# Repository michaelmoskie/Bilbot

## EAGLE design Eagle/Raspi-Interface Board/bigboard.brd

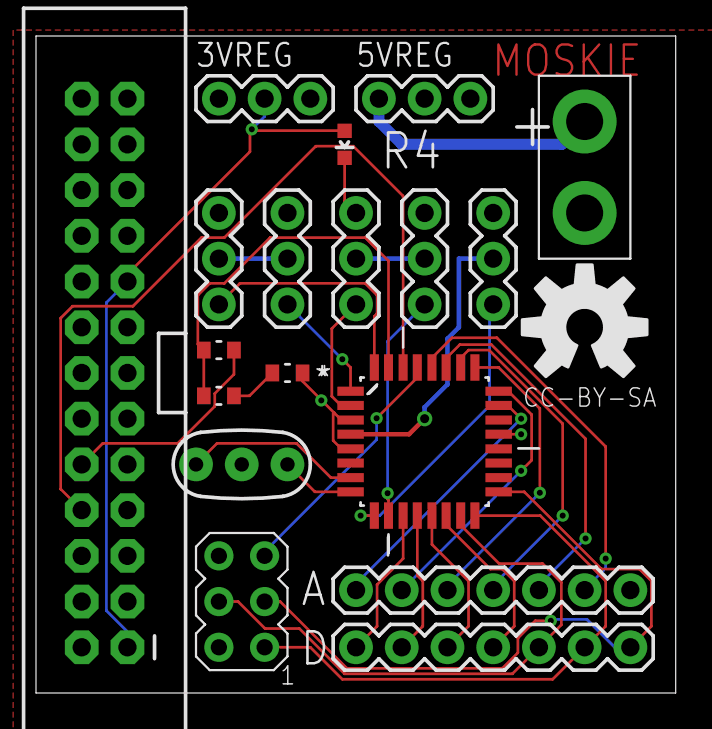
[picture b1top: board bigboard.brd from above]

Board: 2 copper layers, 35.5 x 36.5 mm, 19 parts (0 on the bottom side), 29 nets.

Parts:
3VREG, 5VREG: 1X03
D8: BLUE; LED-0603
ISP1: AVRISP-6; AVRISP
JP1: RASPBERRYPI-GPIOPTH; 2X13-SHROUDED
JP2: M02PTH4; 1X02_XTRA_BIG
JP3, JP4: 1X07
M1, M2, M3, M4, M5: SMALL_SERVO; 1X03
R1, R2, R3: 4.7K Ohms; RESC1608X60N
U1: ATMEGA328P-AU; QFP80P900X900X120-32N
U$1: OSHW-LOGO-L
Y1: RESONATOR-PTH

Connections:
3V: 3VREG.2, D8.A, JP1.1, JP1.17
5V: 3VREG.3, 5VREG.3, ISP1.2, JP1.2, JP1.4, M1.2, M2.2, M3.2, M4.2, M5.2, U1.4, U1.6, U1.18
A0: JP3.1, U1.23
A1: JP3.2, U1.24
A2: JP3.3, U1.25
A3: JP3.4, U1.26
A4: JP3.5, U1.27
A5: JP3.6, U1.28
ARX: JP1.8, U1.30
ATX: R1.1, R2.1, U1.31
D2: M1.1, U1.32
D3: M2.1, U1.1
D4: M3.1, U1.2
D5: M4.1, U1.9
D6: M5.1, U1.10
D7: JP4.1, U1.11
D8: JP4.2, U1.12
D9: JP4.3, U1.13
D10: JP4.4, U1.14
D11: ISP1.4, JP4.5, U1.15
D12: ISP1.1, JP4.6, U1.16
D13: ISP1.3, JP4.7, U1.17
GND: 3VREG.1, 5VREG.2, D8.C, ISP1.6, JP1.6, JP1.9, JP1.14, JP1.20, JP1.25, JP2.2, JP3.7, M1.3, M2.3, M3.3, M4.3, M5.3, R3.1, U1.3, U1.5, U1.21, Y1.2
unnamed: R2.2, R3.2
RESET: ISP1.5, U1.29
RRX: JP1.10, R1.2
VIN: 5VREG.1, JP2.1
XTAL1: U1.7, Y1.1
XTAL2: U1.8, Y1.3

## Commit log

2014-05-05 Top directory structure
    Setting some organization before we start.
2014-05-07 Electronics R1 Commit
    Added Raspi expansion board.
2014-05-20 AVR ISP pins corrected
    In the R1 of the board the AVR ISP pins were totally attached to the
    wrong. 13 != 3. Double check work done at 4AM next time.
2014-05-22 Half edge image
2014-05-23 Added Face detection. Additionally added revision one of the important script Dew Detection. Dew logo included. Miker out.
2014-05-25 Board Update
    New Board revision to fix the 3v3 regulator pinout.
2014-05-26 Added some files and changed some thangs.
2014-07-19 Python API added
    Added initial commit of serial API for communicating with the AtMega328
2014-07-19 Eagle
2014-07-19 Restructure
2014-07-19 Updated API with self and added latest build of core application.
2014-07-19 Actually updating API
2014-07-19 Fixed that there serial buffer overflow and what nots
2014-07-19 Serial commands reduced to chars
2014-07-21 Arduino sketch update to match API
2014-07-28 Added Alpha Test One of dew detection software OpenCV edition
2014-08-02 Updated to a better but still not fully working, nor completed version.

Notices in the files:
Eagle/Raspi-Interface Board/bigboard.brd:
CC-BY-SA
parts and their libraries:
SparkFun-Boards: Licensing: CC v3.0 Share-Alike You are welcome to use this library for commercial purposes.
